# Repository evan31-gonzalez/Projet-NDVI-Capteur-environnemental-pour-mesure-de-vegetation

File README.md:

# Projet NDVI : Capteur environnemental pour la vigne

Projet tutoré de développement instrumental, collaboratif entre **CESBIO** et l'**IUT Mesures Physiques**, visant la conception et la réalisation d’un capteur NDVI (Normalized Difference Vegetation Index) destiné au suivi de l’état de la vigne à partir de mesures spectrales.

Le capteur est conçu pour être utilisé en conditions réelles dans les vignes de Gaillac, dans un contexte de suivi agronomique et environnemental.

---

## Objectif du projet
L’objectif du projet est de développer un capteur NDVI à bas coût permettant d’évaluer la vigueur et le développement foliaire de la vigne à partir de mesures spectrales dans le rouge et le proche infrarouge.

Le dispositif vise à fournir des mesures in situ, complémentaires aux méthodes de télédétection satellitaire, et exploitables directement sur le terrain viticole.

---

## Principe de fonctionnement
Le NDVI est calculé à partir des réflectances mesurées dans deux bandes spectrales :
- Rouge : λ ≈ 680 nm  
- Proche infrarouge (PIR) : λ ≈ 810 nm  

La relation utilisée est :

NDVI = (ρPIR − ρRouge) / (ρPIR + ρRouge)

Les données sont acquises par des capteurs spectraux, traitées par un microcontrôleur, puis enregistrées afin de permettre le calcul et l’analyse de l’indice NDVI.

---

## Mesure de la réflectance
Le système utilise deux capteurs spectraux AS7265x afin de dissocier la lumière réfléchie par la vigne de la lumière incidente :

- un capteur orienté vers la vigne, destiné à mesurer la lumière réfléchie par la végétation,
- un capteur orienté vers le ciel, destiné à mesurer la lumière incidente.

Cette configuration permet de corriger les variations d’éclairement naturel (conditions météorologiques, heure de la journée, orientation du capteur) et de calculer une réflectance fiable. Le NDVI est ainsi déterminé à partir de mesures normalisées, comparables dans le temps et entre différentes parcelles.

---

## Matériel utilisé
Le système de mesure repose sur les composants suivants :

- Deux capteurs spectraux AS7265x pour la mesure de la réflectance (vigne / ciel)
- Microcontrôleur Arduino Nano  
- Capteur environnemental BME280 (température, humidité, pression atmosphérique)  
- Capteur inertiel MPU6050 (accéléromètre et gyroscope)  
- Multiplexeur I2C TCA9548A pour la gestion de plusieurs capteurs sur le bus I2C  
- Module horloge temps réel DS3231 pour l’horodatage des mesures  
- Module lecteur de carte SD pour l’enregistrement local des données  

Les mesures sont horodatées et stockées sur carte SD afin de permettre une exploitation ultérieure.

---

## Protocole

Ce protocole décrit la mise en œuvre et l’utilisation du capteur NDVI développé dans le cadre du projet tutoré.
Le dispositif permet de mesurer l’indice de végétation NDVI d’une parcelle viticole à partir de mesures de réflectance
dans le rouge et le proche infrarouge.

Préparation du système
1. Vérifier que l’ensemble des capteurs est correctement câblé à la carte Arduino.
2. Insérer une carte SD formatée dans le lecteur prévu à cet effet.
3. Vérifier le bon branchement du module RTC DS3231 pour l’horodatage des mesures.
4. S’assurer que le boîtier est correctement fermé et que les capteurs spectraux sont dégagés.

Téléversement du programme
1. Ouvrir le logiciel Arduino IDE sur l’ordinateur.
2. Sélectionner la carte *Arduino Nano 33 IoT* dans le menu *Outils > Type de carte*.
3. Sélectionner le port de communication correspondant à la carte.
4. Ouvrir le fichier du programme Arduino du capteur NDVI.
5. Téléverser le programme sur la carte Arduino.

Mise en place sur le terrain
1. Positionner le capteur de manière stable au-dessus de la vigne.
2. Orienter le premier capteur spectral vers la végétation.
3. Orienter le second capteur spectral vers le ciel afin de mesurer la lumière incidente.
4. Vérifier que le capteur reste immobile pendant la phase de mesure.

Exploitation des données
1. Retirer la carte SD après la fin des mesures.
2. Insérer la carte SD dans un ordinateur.
3. Récupérer les fichiers CSV enregistrés grâce à la carte SD qui affiche les données sous forme de tableau.
4. Utiliser les scripts Python fournis pour :
   - afficher les données,
   - tracer l’évolution du NDVI en fonction du temps.

---

## Entretien et précautions
- Nettoyer régulièrement les capteurs spectraux pour éviter toute perturbation des mesures.
- Vérifier l’état de charge de la batterie avant chaque campagne de mesure.
- Éviter l’exposition prolongée à l’humidité ou à des températures extrêmes sans protection adaptée.
- Couper l’alimentation avant toute manipulation interne du système.

---

## Outils de conception et de développement
Le projet s’appuie sur les outils suivants :

- Eagle pour la conception des schémas électroniques et des cartes PCB  
- Fusion 360 pour la modélisation 3D du boîtier et des supports mécaniques  
- Arduino IDE pour le développement du code embarqué  

---

## Travaux réalisés
Le projet comprend :
- la conception électronique du capteur,
- la programmation embarquée,
- la modélisation 3D du boîtier,
- la conception de cartes PCB,
- la soudure et l’intégration de l’ensemble des capteurs sur support provisoire, réalisées avant la réception du PCB afin de valider le fonctionnement du système,
- l’intégration des différents capteurs,
- l’étalonnage et les tests du dispositif,
- l’exploitation et la visualisation des données acquises.

---

## Organisation du dépôt
- /code/arduino : code embarqué Arduino
- /code/python : scripts Python de visualisation et d’exploitation des données
- /pcb : schémas et fichiers de conception PCB
- /3D : modèles 3D du boîtier et des supports
- /docs : documentation, comptes rendus et supports de présentation

---

## Contexte expérimental
Ce projet est réalisé dans le cadre du BUT Mesures Physiques (Techniques d’Instrumentation).

Les campagnes de mesures terrain sont prévues sur des parcelles de vigne situées à Gaillac, avec des phases de tests, d’étalonnage et de validation prévues à partir de mars 2026.

---

## Équipe – Groupe 1
- Evan GONZALEZ
- Félix GRUÈS  
- Yannis FABRE  
- Sandro BARROT  
- Taha GHISSASSI  

---

## Encadrement
Projet encadré par :
- Mme Aurore Brut  
- M. Jean-Pascal Dezalay

---

## Licence
Ce projet est distribué sous licence MIT.

---

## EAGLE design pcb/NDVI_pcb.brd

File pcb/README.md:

# Carte électronique (PCB)

Ce dossier contient les fichiers de conception de la carte électronique du capteur NDVI.

La carte est conçue sous Eagle et regroupe :
- les deux capteurs spectraux AS7265x (vigne / ciel),
- l’Arduino Nano,
- le multiplexeur I2C TCA9548A,
- le capteur BME280,
- le MPU6050,
- le module RTC DS3231,
- le lecteur de carte SD.

Les fichiers .sch et .brd doivent toujours être utilisés ensemble.

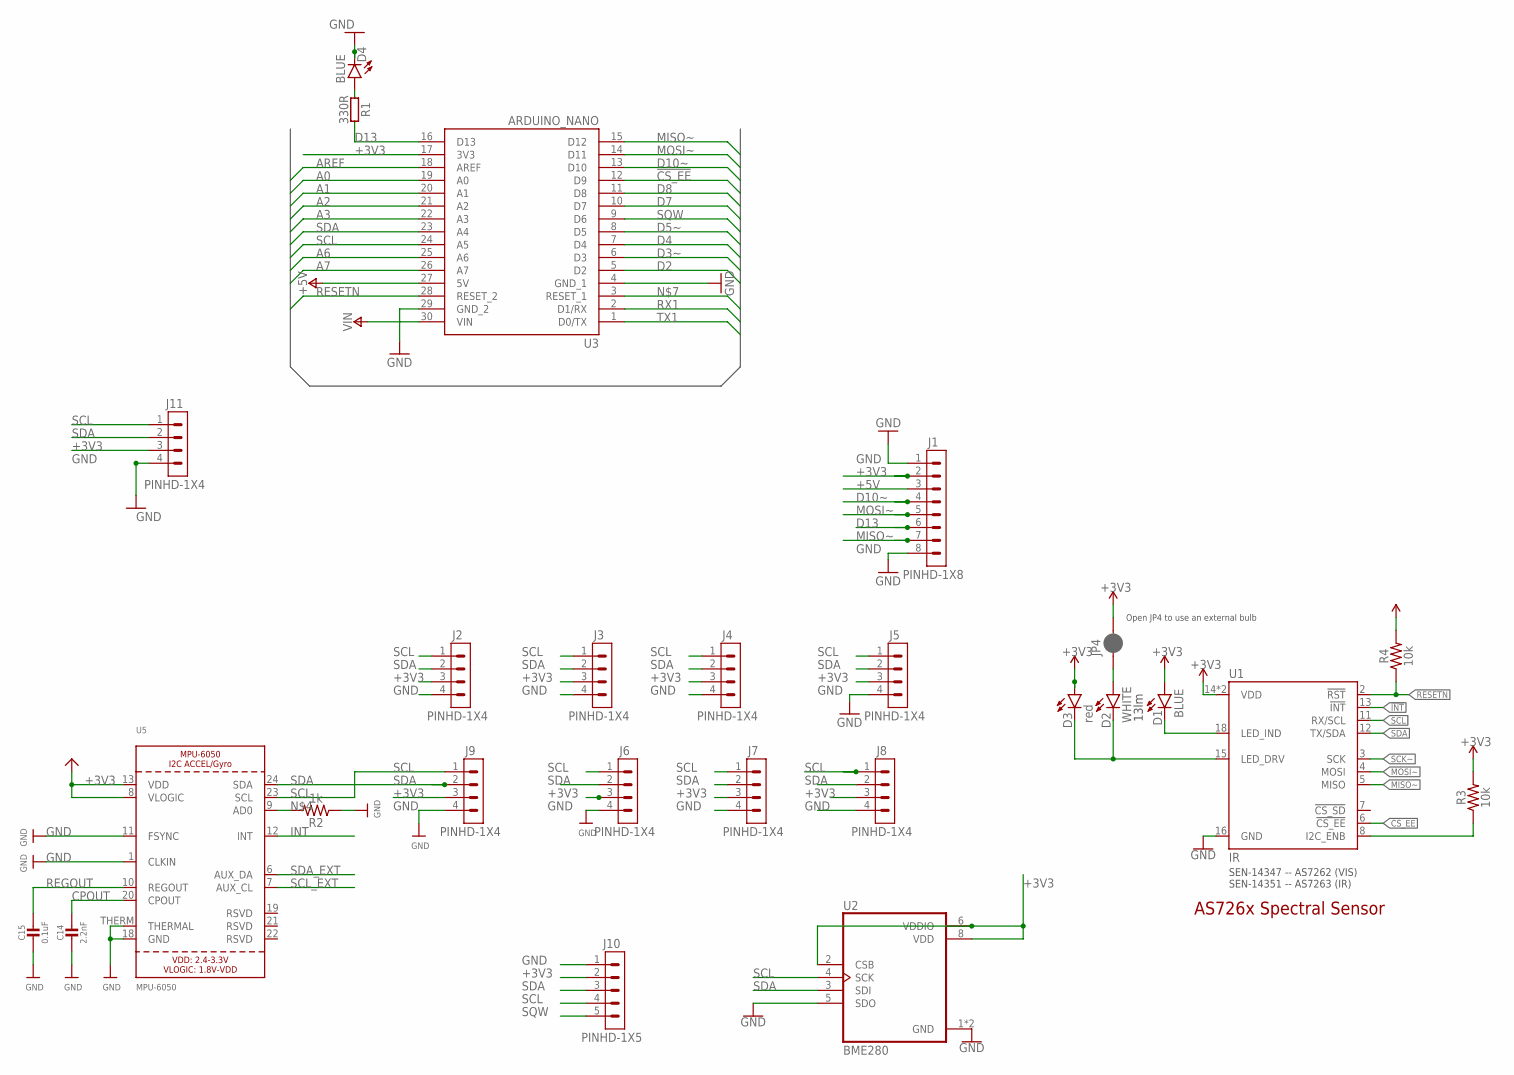
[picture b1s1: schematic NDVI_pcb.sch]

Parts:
C14: 2.2nF; 0603-NO
C15: 0.1uF; 0603-NO
D1, D4: BLUE; LED-0603
D2: WHITE; LED-0603
D3: red; LED-0603
J1: PINHD-1X8; 1X08
J2, J3, J4, J5, J6, J7, J8, J9, J11: PINHD-1X4; 1X04
J10: PINHD-1X5; 1X05
JP4: JUMPER-SMT_2_NC_PASTE_NO-SILK; SMT-JUMPER_2_NC_PASTE_NO-SILK
R1: 330R; C0603
R2: 1k; 0603
R3, R4: 10k; 0603
U1: IR; LGA20
U2: BME280; PSON65P250X250X100-8N
U3: ARDUINO_NANO; MODULE_ARDUINO_NANO_|_A000005
U5: MPU-6050; QFN24_4MM_SMSC

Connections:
!CS_EE: U1.6 (!CS_EE), U3.12 (D9)
!INT: U1.13 (!INT)
+3V3: D1.A, D3.A, J1.2, J2.3, J3.3, J4.3, J5.3, J6.3, J7.3, J8.3, J9.3, J10.2, J11.3, JP4.2, R3.2, R4.2, U1.14 (VDD), U1.17 (VDD), U2.2 (CSB), U2.6 (VDDIO), U2.8 (VDD), U3.17 (3V3), U5.8 (VLOGIC), U5.13 (VDD)
+5V: J1.3, U3.27 (5V)
A0: U3.19 (A0)
A1: U3.20 (A1)
A2: U3.21 (A2)
A3: U3.22 (A3)
A6: U3.25 (A6)
A7: U3.26 (A7)
AREF: U3.18 (AREF)
CPOUT: C14.1, U5.20 (CPOUT)
D2: U3.5 (D2)
D3~: U3.6 (D3)
D4: U3.7 (D4)
D5~: U3.8 (D5)
D7: U3.10 (D7)
D8: U3.11 (D8)
D10~: J1.4, U3.13 (D10)
D13: J1.6, R1.2, U3.16 (D13)
GND: C14.2, C15.2, D4.C, J1.1, J1.8, J2.4, J3.4, J4.4, J5.4, J6.4, J7.4, J8.4, J9.4, J10.1, J11.4, R2.1, U1.16 (GND), U2.1 (GND), U2.5 (SDO), U2.7 (GND), U3.29 (GND_2), U5.1 (CLKIN), U5.11 (FSYNC), U5.18 (GND), U5.THERM (THERMAL)
INT: U5.12 (INT)
LED_DRV: D2.C, D3.C, U1.15 (LED_DRV)
MISO~: J1.7, U1.5 (MISO), U3.15 (D12)
MOSI~: J1.5, U1.4 (MOSI), U3.14 (D11)
unnamed: R3.1, U1.8 (I2C_ENB)
unnamed: D1.C, U1.18 (LED_IND)
unnamed: D4.A, R1.1
unnamed: R2.2, U5.9 (AD0)
unnamed: D2.A, JP4.1
REGOUT: C15.1, U5.10 (REGOUT)
RESETN: R4.1, U1.2 (!RST), U3.28 (RESET_2)
RX1: U3.2 (D1/RX)
SCK~: U1.3 (SCK)
SCL: J2.1, J3.1, J4.1, J5.1, J6.1, J7.1, J8.1, J9.1, J10.4, J11.1, U1.11 (RX/SCL), U2.4 (SCK), U3.24 (A5), U5.23 (SCL)
SCL_EXT: U5.7 (AUX_CL)
SDA: J2.2, J3.2, J4.2, J5.2, J6.2, J7.2, J8.2, J9.2, J10.3, J11.2, U1.12 (TX/SDA), U2.3 (SDI), U3.23 (A4), U5.24 (SDA)
SDA_EXT: U5.6 (AUX_DA)
SQW: J10.5, U3.9 (D6)
TX1: U3.1 (D0/TX)
VIN: U3.30 (VIN)

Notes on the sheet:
AS726x Spectral Sensor
Open JP4 to use an external bulb
13lm
SEN-14347 -- AS7262 (VIS) SEN-14351 -- AS7263 (IR)

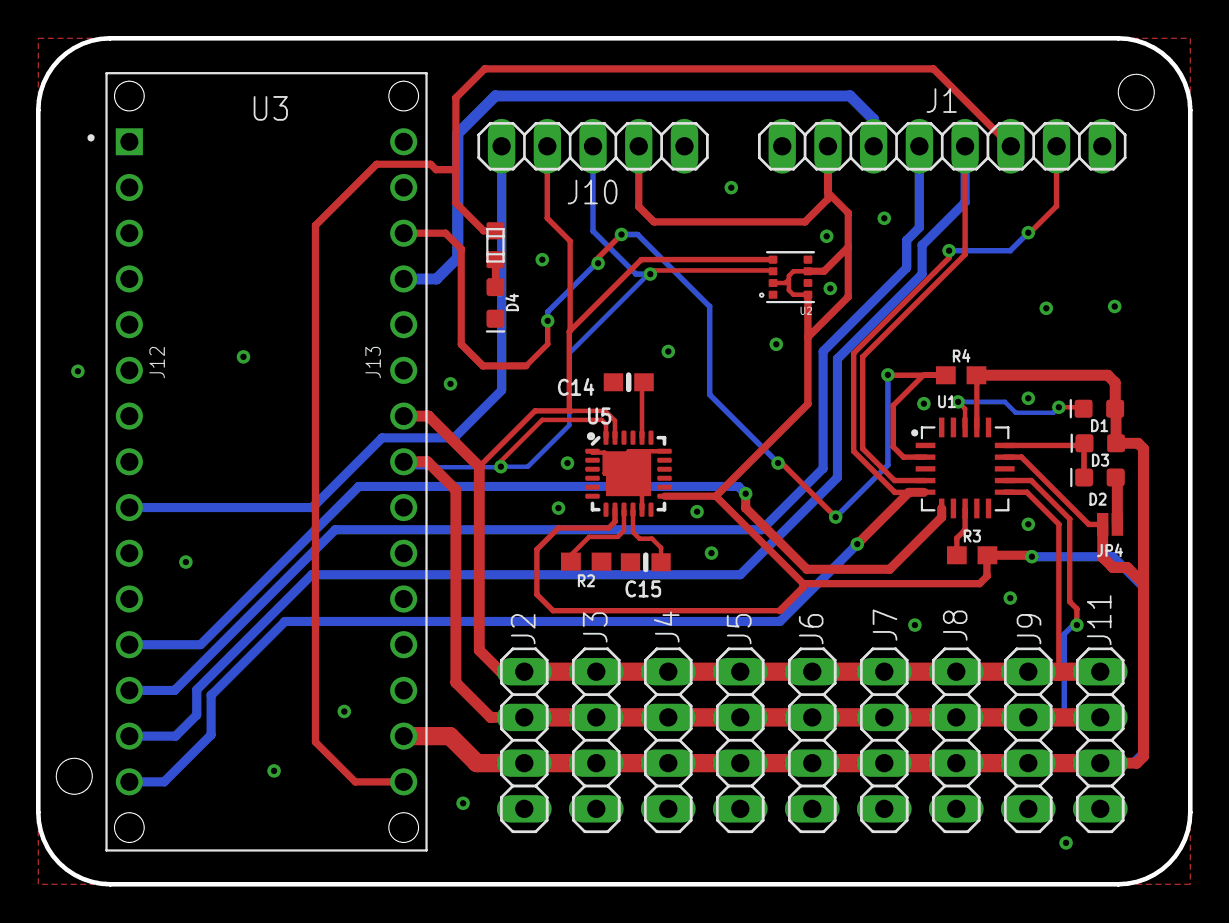
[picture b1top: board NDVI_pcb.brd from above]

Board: 2 copper layers, 64.0 x 47.0 mm, 26 parts (0 on the bottom side), 20 nets.

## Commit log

2026-01-20 Update LICENSE
2026-01-20 README principal du projet
2026-01-20 Ajout du README du dossier pcb
2026-01-20 Version finale du PCB
2026-01-20 Ajout du README du dossier pcb/exports
2026-01-20 Ajout du schéma et du PCB (top et bottom)
2026-01-20 Ajout du README du dossier code
2026-01-20 Ajout du README du dossier code/arduino
2026-01-20 Ajout du code Arduino v0.1 pour l’acquisition NDVI
2026-01-20 Ajout du README du dossier code/python
2026-01-20 Ajout du README du dossier 3D
2026-01-20 Ajout du README du dossier 3D/fusion
2026-01-20 Ajout du README du dossier 3D/exports
2026-01-20 Ajout du README du dossier 3D/images
2026-01-20 Initialisation du dossier documentation du projet
2026-01-20 Ajout du README du dossier comptes_rendus
2026-01-20 README du dossier presentation
2026-01-20 Ajout du README du dossier images
2026-01-20 Ajout du modèle Fusion 360 du boîtier v0.1
2026-01-20 Ajout des images du boîtier 3D v0.1
2026-01-20 Ajout des exports 3D du boîtier v0.1
2026-01-20 Création du README du dossier code
2026-01-21 Ajout du README principal du projet
2026-01-22 Modification du README
    Updated the description of Python scripts for data exploitation.
2026-01-22 Modification du README, Bibliothèques python
2026-01-22 Modification README, ajouts bibliothèques
    Added a section detailing the libraries used in the project.
2026-01-22 Modification du README
2026-01-22 Ajout des v0.2
2026-01-22 Ajout de la v0.2
2026-01-22 Ajout de la v0.3
2026-01-22 Ajout protocole README
    Added detailed protocol for NDVI sensor implementation and usage.
2026-01-22 Ajout
    Removed data acquisition section and adjusted headings.
2026-01-22 Ajout protocole README
    Added detailed protocol for NDVI sensor implementation, including system preparation, program upload, field setup, and data exploitation.
2026-01-22 Bibliothèques Python
    Added mention of 're' module for reading Arduino.
2026-01-22 Modification du README principal du projet (protocole)
    Updated section headings and clarified data retrieval instructions.
2026-01-22 Ajout des codes python (v0.1 et v0.2)
2026-01-23 README principal du projet
    Added maintenance and precautions section to README.
2026-01-23 Ajout bibliothèque
2026-01-23 Ajout de la deuxième version du code Arduino
2026-01-23 Ajout c
2026-01-23 Ajout des 3e et 4e versions du code Arduino (SD)
2026-01-23 Ajout diapo
2026-01-23 Ajout de la dernière version du code arduino sur le README
2026-01-23 Update README with SD and SPI library details
    Added information about SD and SPI libraries for data management.
2026-01-23 Ajout du deuxième code python dans le README.md
2026-01-23 Modification du README python.md
2026-02-12 Ajout d'une première version de métrologie
2026-02-12 Ajout du choix des axes x et y Python

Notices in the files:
parts and their libraries:
microbuilder: This work is placed in the public domain, and may be freely used for commercial and non-commercial work with the following conditions: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
SparkFun-LED: Licensing: Creative Commons ShareAlike 4.0 International - https://creativecommons.org/licenses/by-sa/4.0
